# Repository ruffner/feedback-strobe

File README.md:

# Feedback Strobe

The Feedback Strobe is a technology demonstration aid for EE422G Signals and Systems Laboratory at the University of Kentucky. Commisioned by [Dr. Kevin Donohue](https://www.engr.uky.edu/research/researchers/kevin-donohue/) and [Dr. Michael Johnson](https://www.engr.uky.edu/research/researchers/michael-t-johnson/), the device facilitates hands on involvement in many aspects of a persistence of vision project. The students will be tasked with programming an ARM microcontroller using the Arduino IDE to control both rotation and blink speed of the device in order to produce a persistence of vision effect.

## Lab Procedure
### Setup
#### Basic tools, supplies
Gonna need some wire. Maybe some pliers for the wires that got tinned super heavy, these breadboards are tight. A bench power supply will be necessary after the all the connections have been made. 

When determining the rotation speed, an oscilloscope will probably be handy to for characterizing the output of the reflectance sensor.

#### IDE
A computer with a working install of the [Arduino IDE](https://www.arduino.cc/en/Main/Software) will also be necessary. For the PID part of the lab, a library will have to be installed. [Here](https://www.arduino.cc/en/Guide/Libraries) is a guide on how this is done.

#### Adding Teensy support
For the Arudino IDE to support cross compiling to the CortexM on the Teensy, Paul Stoffregen's [Teensyduino add-on](https://www.pjrc.com/teensy/teensyduino.html) must be downloaded and installed. All platforms are supported. Point the installer at your copy of the IDE and let it install the necessary tools. 
 
Now, in the *Tools > Board:* menu of the Arduino IDE, a 'Teensy 3.2 / 3.1' option will exist. Choose it. Now make sure you can see an available corresponding serial port in the *Tools > Port* menu. reset the Teensy if it doesn't show.

### LED and IR Sensor Setup
First, the leads of the LED must be mapped to [Teensy 3.2](https://www.sparkfun.com/products/13736) pin numbers. The Figure below shows the color coding of the slip ring wires. Make sure to connect the output of the reflectance sensor to a pin with ```analogRead()``` capabilities.

#### Parts and layout

There is an [analog reflectance sensor](https://www.sparkfun.com/products/9453) on the underside of the propellor who's signal (the white slip ring wire) varies upon rotation of the propellor. The white pulley on the motor shaft provides a high reflectance surface causing the output of the IR reflectance sensor to decrease. Thus, the analog signal will have local minima upon completion of a rotation.

Slip ring wires can be pinned under the Teensy upon insertion into the breadboard. This eases the breadboarding process. 

#### Teensy pinout
Any GPIO on the [Teensy pins](https://www.pjrc.com/teensy/card7a_rev1.png) can be used for driving the LEDs.

#### Powering the reflectance sensor
The IR reflectance sensor can be powered from the Teensy's onboard 3.3V regulator. It is *NOT* a 5V tolerant IC!

Make sure the reflectance sensor output voltage is least when over the drive pulley. Test that all of the LEDs can be turned both on and off.

### Back EMF Protection and Motor Circuit

The schematic below shows the ciruit to build to interface with the motor. The two thicker red (+) and blue(-) wires are not part of the slip ring 12, they are the motor wires. Connect the (-) to the drain of the MOSFET. 

Parts supplied to build this circuit are as follows:
 - 1x [STP60N N channel MOSFET](http://www.st.com/content/ccc/resource/technical/document/datasheet/95/a9/32/90/53/2f/44/4f/CD00154892.pdf/files/CD00154892.pdf/jcr:content/translations/en.CD00154892.pdf)
 - 1x [7805 5V Regulator](https://www.sparkfun.com/datasheets/Components/LM7805.pdf)
 - 1x [1N400x Diode](http://www.onsemi.com/pub/Collateral/1N4001-D.PDF) (Will have to find another in the lab.)
 - 1x 1.5 uF ceramic capacitor
 - 1x 0.1 uF ceramic capacitor
 - 1x 58 Ohm resistor
 - 1x 10 kOhm resistor
 
#### Power
The bench power supply should be set to 9 volts
 
The Teensy is powered from the ouput of the 5V regulator and should be attached to  *Vin* pin on the Teensy.

Make sure to common ground the bench supply and Teensy.

#### PWM Setup
Any pin on the Teensy shown with PWM capability may be used to drive the gate of the MOSFET.

Keep in mind the smallest PWM value will probably not be enough to break the stall torque of the motor, so a baseline minimum PWM that will start the motor will need to be establised.

### Programming Tasks
In order for the motor speed to track the blink rate, [PID controller](https://en.wikipedia.org/wiki/PID_controller) must be implemented. There is a handy [PID Library](https://playground.arduino.cc/Code/PIDLibrary) for this exact purpose, with helpful examples for setting up a basic plant.

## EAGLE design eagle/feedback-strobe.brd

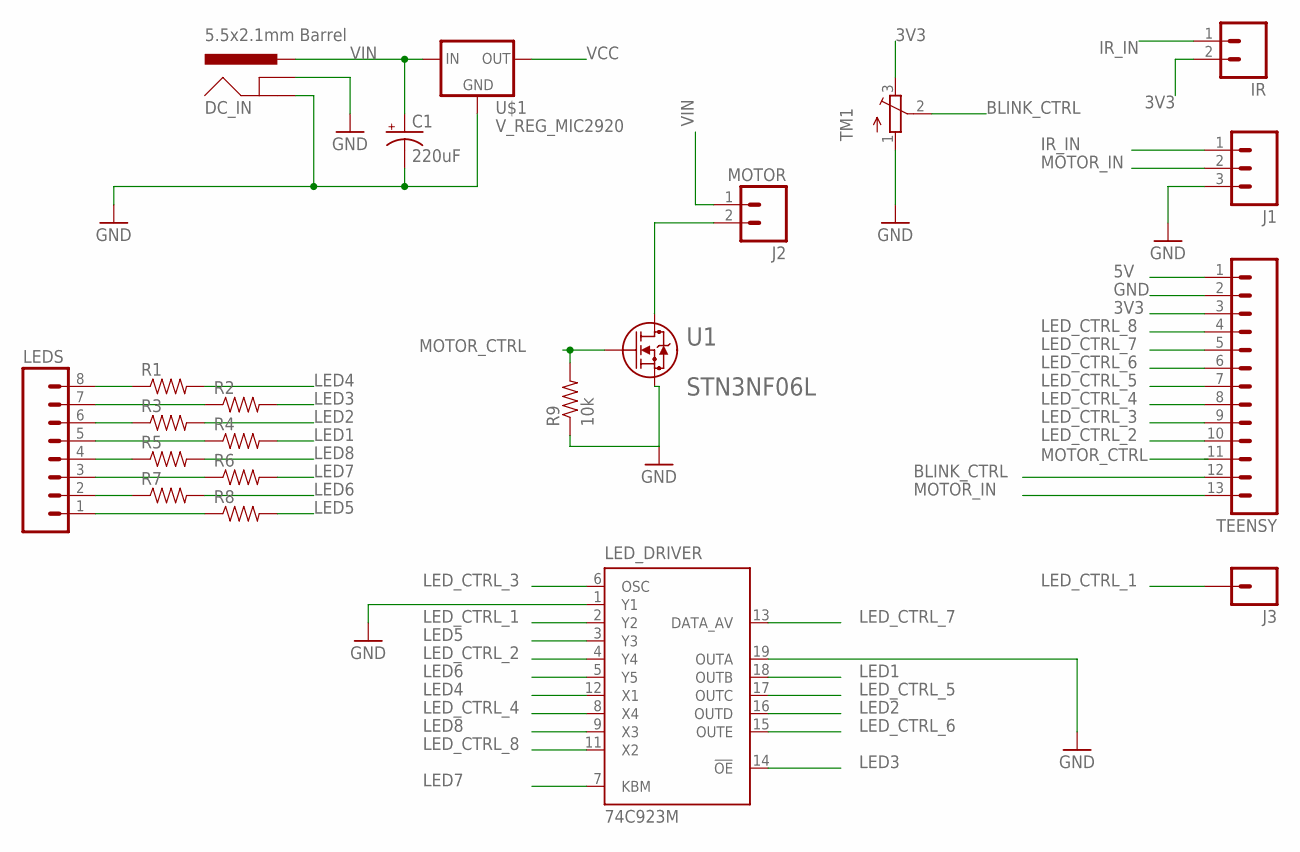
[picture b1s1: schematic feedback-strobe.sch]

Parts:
C1: 220uF; NIPPON_F80
DC_IN: 5.5x2.1mm Barrel; POWER_JACK_SMD
IR: M02PTH; 1X02
J1: M03PTH; 1X03
J2: MOTOR; 1X02
J3: M01PTH; 1X01
LEDS: M08; 1X08_ROUND
LED_DRIVER: 74C923M; SO20W
R1, R2, R3, R4, R5, R6, R7, R8: RESISTOR0603-RES; 0603-RES
R9: 10k; 0603-RES
TEENSY: M13; 1X13
TM1: TRIMPOT3386; TRIM-3386
U1: STN3NF06L; SOT-223
U$1: V_REG_MIC2920; SOT223

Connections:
3V3: IR.2, TEENSY.3, TM1.3 (E)
5V: TEENSY.1
BLINK_CTRL: TEENSY.12, TM1.2 (S)
GND: C1.-, DC_IN.GND (GNDBREAK), DC_IN.P$4 (GND), J1.3, LED_DRIVER.1 (Y1), LED_DRIVER.10 (GND), LED_DRIVER.19 (OUTA), R9.1, TEENSY.2, TM1.1 (A), U1.3, U$1.2 (GND)
IR_IN: IR.1, J1.1
LED1: LED_DRIVER.18 (OUTB), R4.2
LED2: LED_DRIVER.16 (OUTD), R3.2
LED3: LED_DRIVER.14 (!OE), R2.2
LED4: LED_DRIVER.12 (X1), R1.2
LED5: LED_DRIVER.3 (Y3), R8.2
LED6: LED_DRIVER.5 (Y5), R7.2
LED7: LED_DRIVER.7 (KBM), R6.2
LED8: LED_DRIVER.9 (X3), R5.2
LED_CTRL_1: J3.1, LED_DRIVER.2 (Y2)
LED_CTRL_2: LED_DRIVER.4 (Y4), TEENSY.10
LED_CTRL_3: LED_DRIVER.6 (OSC), TEENSY.9
LED_CTRL_4: LED_DRIVER.8 (X4), TEENSY.8
LED_CTRL_5: LED_DRIVER.17 (OUTC), TEENSY.7
LED_CTRL_6: LED_DRIVER.15 (OUTE), TEENSY.6
LED_CTRL_7: LED_DRIVER.13 (DATA_AV), TEENSY.5
LED_CTRL_8: LED_DRIVER.11 (X2), TEENSY.4
MOTOR_CTRL: R9.2, U1.1
MOTOR_IN: J1.2, TEENSY.13
unnamed: LEDS.8, R1.1
unnamed: LEDS.7, R2.1
unnamed: LEDS.6, R3.1
unnamed: J2.2, U1.2
unnamed: LEDS.1, R8.1
unnamed: LEDS.2, R7.1
unnamed: LEDS.4, R5.1
unnamed: LEDS.3, R6.1
unnamed: LEDS.5, R4.1
VCC: LED_DRIVER.20 (VCC), U$1.3 (OUT)
VIN: C1.+, DC_IN.VIN0 (PWR), J2.1, U$1.1 (IN)

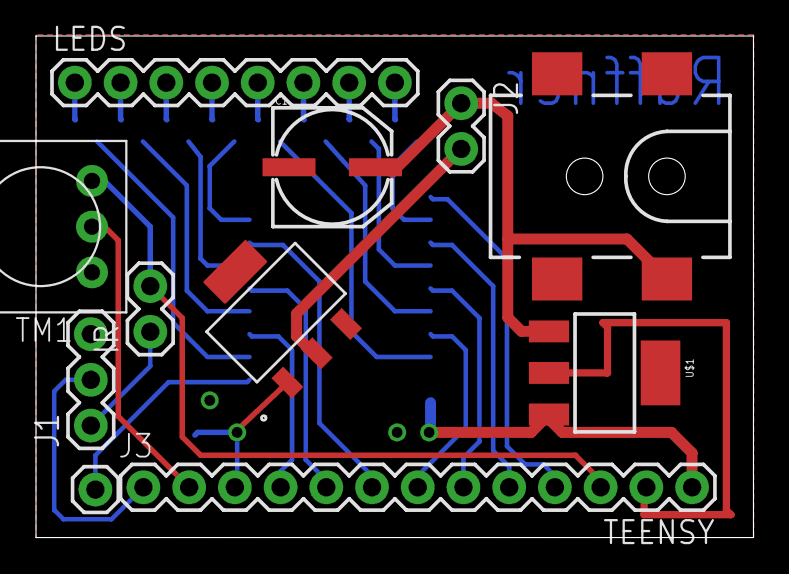
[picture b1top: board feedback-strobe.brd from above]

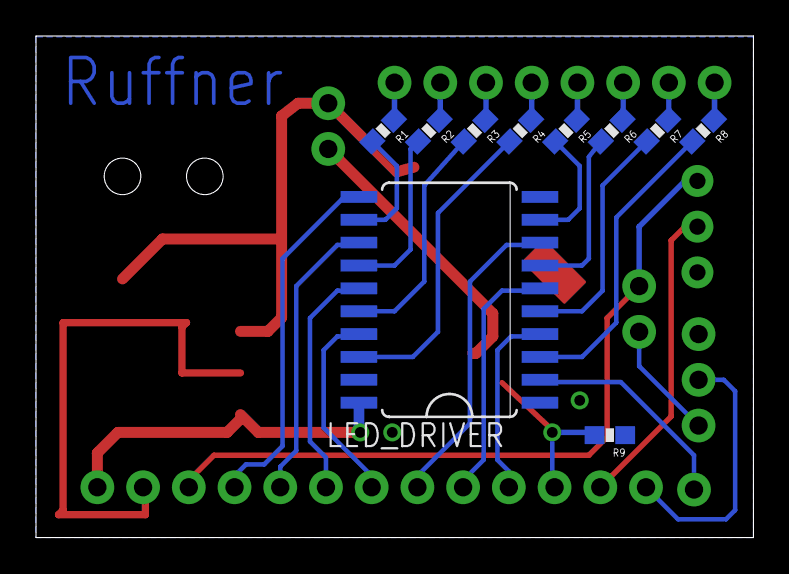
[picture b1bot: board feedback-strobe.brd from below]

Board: 2 copper layers, 39.9 x 27.9 mm, 21 parts (10 on the bottom side), 33 nets.

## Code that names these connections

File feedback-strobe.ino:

// FEEDBACK STROBE V2 
// MATT RUFFNER 
// NOVEMBER 2017

#include <TimerOne.h>
#include <PID_v1.h>

//Define PID variables
double Setpoint, Input, Output;

// NUMBER OF LEDS
#define NLEDS 8

//Specify the links and initial tuning parameters
double Kp=.5, Ki=0, Kd=0;
PID myPID(&Input, &Output, &Setpoint, Kp, Ki, Kd, DIRECT);

/*------------------------------*/
/* HARDWARE CONNECTIONS         */
/*------------------------------*/
// INDIVIDUAL LED CONNECTIONS
#define LED1  12
#define LED2  11
#define LED3  10
#define LED4  9
#define LED5  17
#define LED6  16
#define LED7  15
#define LED8  14

// TO EASE ITERATIONS
const uint8_t leds[] = {LED1, LED2, LED3, LED4, LED5, LED6, LED7, LED8};

/* PWM SIGNAL TO MOSFET */
#define MOTOR_PIN 6

/* IR REFLECTANCE SENSOR ANALOG IN */
#define IR_PIN    23//A9
#define IR_SAMPLE_PERIOD 5000 // ISR PERIOD IN MICROSECONDS
#define IR_SAMPLE_COUNT 200
float irSamples[IR_SAMPLE_COUNT];
unsigned long irSampleIndex = 0;
volatile unsigned long lastIrMinTimestamp = 0;
volatile unsigned long lastRotationPeriod = 0;
float currentRotationFreq = 0;


// LED BLINK CONTROL VARIABLES
bool ledState = LOW;
unsigned long lastStrobeTime = 0; 
unsigned long strobeOffTime = 120; 
unsigned long strobeOnTime =  5;

double blinkFreq = 1.0 / ((strobeOnTime + strobeOffTime)/1000.0);

volatile bool started = 0;
volatile bool newFreq = 0;

#define DEBUG 1

void setup()
{
  Serial.begin(9600);
  
  // SET LEDS AS OUTPUTS AND TURN THEM OFF
  if( DEBUG ) Serial.println("Setting LEDs as outputs...");
  for (uint8_t i=0; i<NLEDS; i++ ){
    pinMode(leds[i], OUTPUT);
    digitalWrite(leds[i], LOW);
  }


  // SET MOTOR AS OUTPUT, TURN OFF
  if( DEBUG ) Serial.println("Initializing motor as output...");
  pinMode(MOTOR_PIN, OUTPUT);
  //driveMotor(255);


  // SET REFLECTANCE SENSOR AS INPUT
  if( DEBUG ) Serial.println("Setting up analog input sampling...");
  pinMode(IR_PIN, INPUT);
  Timer1.initialize(IR_SAMPLE_PERIOD);
  Timer1.attachInterrupt(sampleIRSensor);

  Serial.println("Setting PID variables");
  Input = currentRotationFreq;
  Setpoint = map(blinkFreq*10, 0, 150, 0, 2550)/10.0;
  myPID.SetOutputLimits(150,255);
  myPID.SetMode(AUTOMATIC);

  Serial.println("Starting...");

  driveMotor(200);
}

unsigned long lastFreqUpdate = 0;

void loop() 
{
  // put your main code here, to run repeatedly:

  if( millis() - 1000 > lastFreqUpdate ){

    noInterrupts();
    double t = currentRotationFreq;
    interrupts();
    
    Serial.print("current rot freq: ");
    Serial.println(t);
    lastFreqUpdate = millis();

    Input = map(t*10, 0, 150, 0, 2550)/10.0;

    myPID.Compute();
    
    Serial.print("new PID output: ");
    Serial.println(Output);

    driveMotor(Output);
  }

  
//  // UPDATE ROTATION SPEED
//  if( started && newFreq ){ 
//    noInterrupts();
//    Serial.print("rot freq: ");
//    Serial.println(currentRotationFreq);
//
//    
//    newFreq = 0;
//  }


  // drive LEDs
  if( millis() - lastStrobeTime > ( ledState ? strobeOnTime : strobeOffTime ) ){
    // update timestamp
    lastStrobeTime = millis();
    
    toggleStrobe();
  }

}

void sampleIRSensor()
{
  static bool state = 0;
  uint16_t n = (irSampleIndex++) % 200;
  irSamples[n] = (map(analogRead(IR_PIN), 0, 1023, 0, 10000)-5000)/10000.0;

  // with ir in from -0.5-0.5, dIr_dt can range from -50 to 50 
  if( irSampleIndex > 0 ){
    // derivative 2 most recent IR readings
    float dirdt = (irSamples[n]-irSamples[n-1]) / (IR_SAMPLE_PERIOD * 0.000001);
    unsigned long rn = millis();

    // trigger once a negative slope above a threshold is reached
    // when a positive dirdt is found it will be at the valley of the signal dip
    switch( state ){
    case 0:
      if( dirdt < -5 ){
        state = 1;
      }
      break;
    case 1:
      if( dirdt > 0 ){
        lastRotationPeriod = rn - lastIrMinTimestamp;
        lastIrMinTimestamp = rn;
        state = 0;
        currentRotationFreq = (float)(1000.0/lastRotationPeriod);
        //Serial.println(currentRotationFreq);
        if( !started ) started = 1;
        //newFreq = 1;
      }
    } 
  }
}

void toggleStrobe()
{
  uint8_t i;
  
  ledState = !ledState;

  for( i=0; i<NLEDS; i++ ){
    digitalWrite( leds[i], ledState );
  }
}

void driveMotor(uint8_t spd)
{
  uint8_t realSpeed = map(spd, 0, 255, 255, 0);
  analogWrite(MOTOR_PIN, realSpeed);
}

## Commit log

2016-10-30 first commit, first iteration of cad drawings and stls
2016-11-01 tweaked motor slot width, shaft adapter flatspot
2016-11-01 removed images since github can render stls
2016-11-01 Created spinning LED arm with cutout for IR reflectance sensor. Testing to see if printed gear teeth will work.
2016-11-04 moved to pulley drive system. added drive pulley to fit on motor
2016-11-07 updated drive pulley
2016-11-07 updated drive pulley shaft depth
2016-11-07 shortened drive pulley
2016-11-08 started on board layout
2016-11-09 finished v1 PCB design
2016-11-22 started on software, added images of v1 pcb layout
2016-11-22 edited mosfet label
2016-11-25 added image of first assembly
2016-12-19 revised mounting base
2016-12-19 added motor securing structural support, revised board mount location, shortened pulley
2016-12-20 added image of v2 body design
2016-12-20 added data flow diagram and corresponding draw.io xml source
2016-12-29 new components added, new board dimensions set. routing started. mosfet footprint from digikey not wanting to connect nets
2016-12-29 initial completion of v2 pcb design
2016-12-29 added dimensions
2017-01-04 shifted teensy mounting location on main base part design. added chamfer to top rim.
2017-01-05 added new voltage regulator, reduced number of vias, added more spacing between traces.
2017-01-05 updated pin defs for v2 board
2017-01-05 added datasheets for ICs
2017-01-05 put my name on the board
2017-01-05 added images of new pcb and finished build
2017-01-05 updated data flow diagram
2017-01-05 added v2.1 pcb images
2017-01-06 strobe rate and motor speed controlled by analog inputs, yet to be tested
2017-01-06 specified voltage range on adc pin
2017-01-07 added PDF of partslist
2017-01-11 added labview test bench
2017-11-13 redesigned mainbase to hold breadboard for lab assembly
2017-11-15 increased shaft size in drive pulley
2017-11-23 added wiring diagram for prop
2017-11-23 updated wiring image
2017-11-23 added new models
2017-11-23 updated image
2017-11-23 added back emf ciircuit
2017-11-24 updated emf protection circuit
2017-11-27 updated emf schematic to include 5v reg
2017-12-06 added beginning of solution
2018-08-12 removed old files

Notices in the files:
parts and their libraries:
SparkFun-Connectors: Licensing: Creative Commons ShareAlike 4.0 International - https://creativecommons.org/licenses/by-sa/4.0
COPYRIGHT: Copyright C 2015 Accelerated Designs. All rights reserved
